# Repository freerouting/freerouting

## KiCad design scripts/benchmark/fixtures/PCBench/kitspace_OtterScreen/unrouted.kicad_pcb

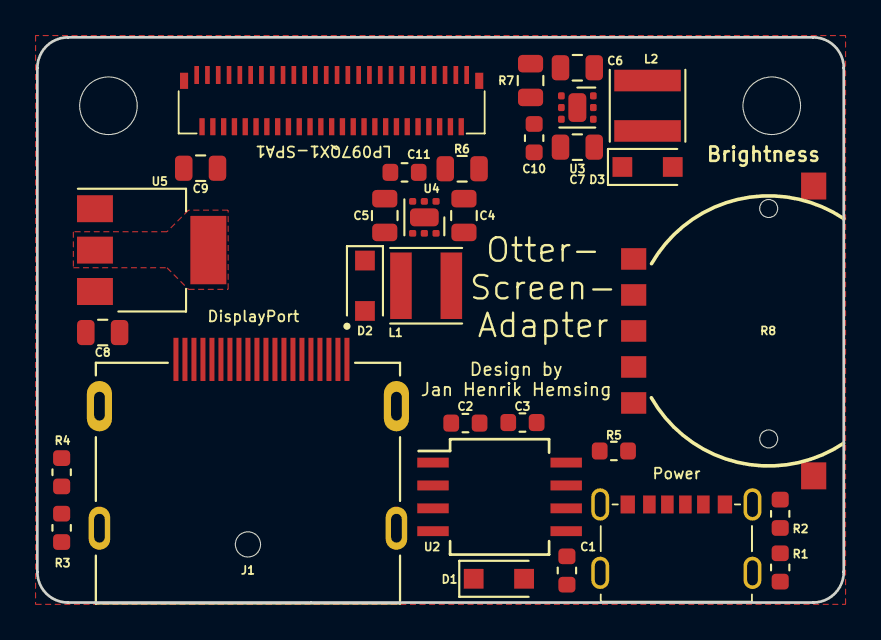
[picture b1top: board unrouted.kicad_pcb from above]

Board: 2 copper layers, 44.8 x 31.4 mm, 33 parts (0 on the bottom side), 31 nets, no tracks yet.

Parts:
C1, C2: 100n; C_0603_1608Metric
C3: 1n; C_0603_1608Metric
C4, C6: 10uF; C_0805_2012Metric
C5, C7, C8, C9: 0.47uF; C_0805_2012Metric
C10, C11: 220nF; C_0603_1608Metric
D1: D; D_SOD-123F
D2, D3: SS34; D_SOD-123F
H1, H2: MountingHole_Pad; MountingHole_3.2mm_M3
J1: 47272-0001; MOLEX_47272-0001
J2: USB-C_Power
L1, L2: 22uH; L_Taiyo-Yuden_MD-4040
R1, R2: 5K1; R_0603_1608Metric
R3, R4: 0; R_0603_1608Metric
R5: 100; R_0603_1608Metric
R6, R7: 0.8; R_0805_2012Metric
R8: RK14J12R0A09
U1: 5022505191
U2: NE555; SO-8_5.3x6.2mm_P1.27mm
U3, U4: TPS61160A; WSON-6-1EP_2x2mm_P0.65mm_EP1x1.6mm
U5: AMS1117-3.3; SOT-223-3_TabPin2

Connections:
+3V3: C9.1, U1.4, U1.5, U1.6, U1.7, U5.2
+5V: C2.1, C4.1, C6.1, C8.1, J2.2, J2.5, L1.1, L2.1, R5.1, U2.4, U2.8, U3.6, U4.6, U5.3
AUX_N: J1.17, U1.10
AUX_P: J1.15, U1.9
GND: C1.2, C2.2, C3.2, C4.2, C5.2, C6.2, C7.2, C8.2, C9.2, C10.2, C11.2, H1.1, H2.1, J1.2, J1.5, J1.8, J1.11, J1.16, J1.19, J1.S1, J1.S2, J1.S3, J1.S4, J2.1, J2.6, J2.7, R1.2, R2.2, R3.2, R4.2, R6.2, R7.2, U1.1, U1.3, U1.8, U1.11, U1.15, U1.19, U1.23, U1.27, U1.28, U1.29, U1.36, U1.43, U1.51, U2.1, U3.3, U3.7, U4.3, U4.7, U5.1
HPD: J1.18, U1.2
L0_N: J1.10, U1.12
L0_P: J1.12, U1.14
L1_N: J1.7, U1.16
L1_P: J1.9, U1.18
L2_N: J1.4, U1.20
L2_P: J1.6, U1.22
L3_N: J1.1, U1.24
L3_P: J1.3, U1.26
LEDA1: C5.1, D2.1, U1.48, U1.49
LEDA2: C7.1, D3.1, U1.45, U1.46
LEDC1: R6.1, U1.37, U1.38, U1.39, U1.40, U1.41, U1.42, U4.1
LEDC2: R7.1, U1.30, U1.31, U1.32, U1.33, U1.34, U1.35, U3.1
unnamed: C1.1, U2.5
unnamed: C3.1, D1.1, R8.1, U2.2, U2.6
unnamed: C10.1, U3.2
unnamed: C11.1, U4.2
unnamed: D1.2, R8.2, U2.7
unnamed: D2.2, L1.2, U4.4
unnamed: D3.2, L2.2, U3.4
unnamed: J1.13, R3.1
unnamed: J1.14, R4.1
unnamed: J2.3, R1.1
unnamed: J2.4, R2.1
unnamed: R5.2, R8.3
PWM: U2.3, U3.5, U4.5

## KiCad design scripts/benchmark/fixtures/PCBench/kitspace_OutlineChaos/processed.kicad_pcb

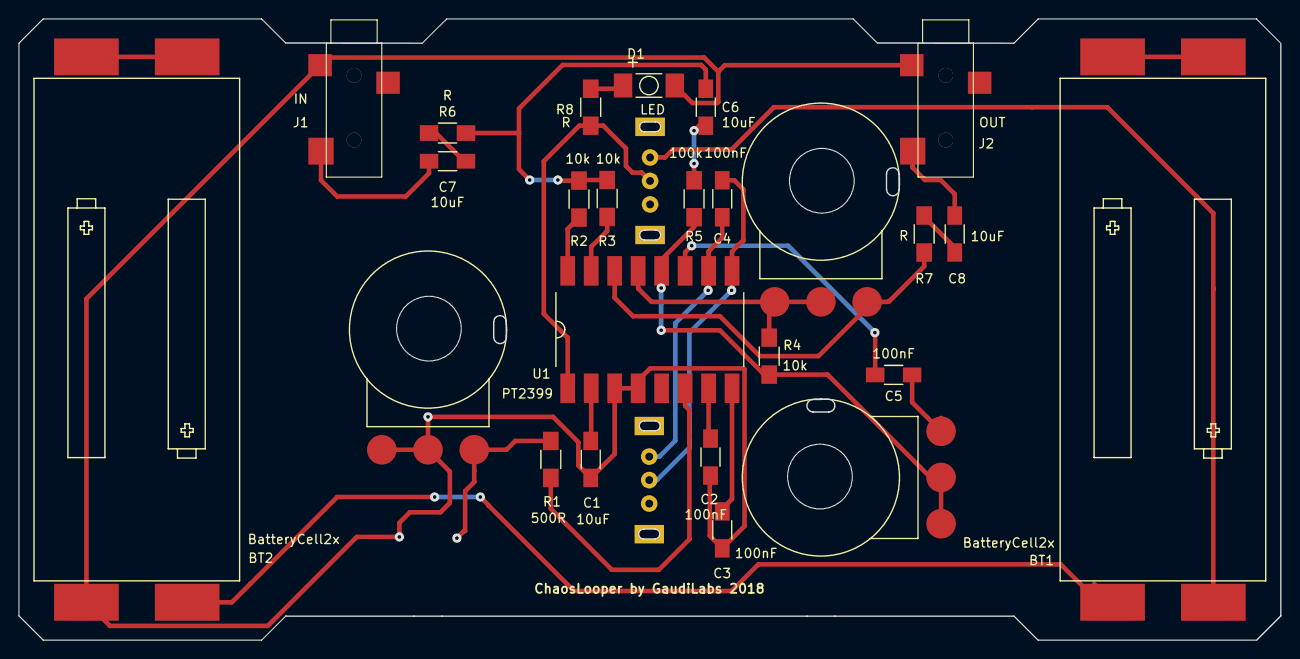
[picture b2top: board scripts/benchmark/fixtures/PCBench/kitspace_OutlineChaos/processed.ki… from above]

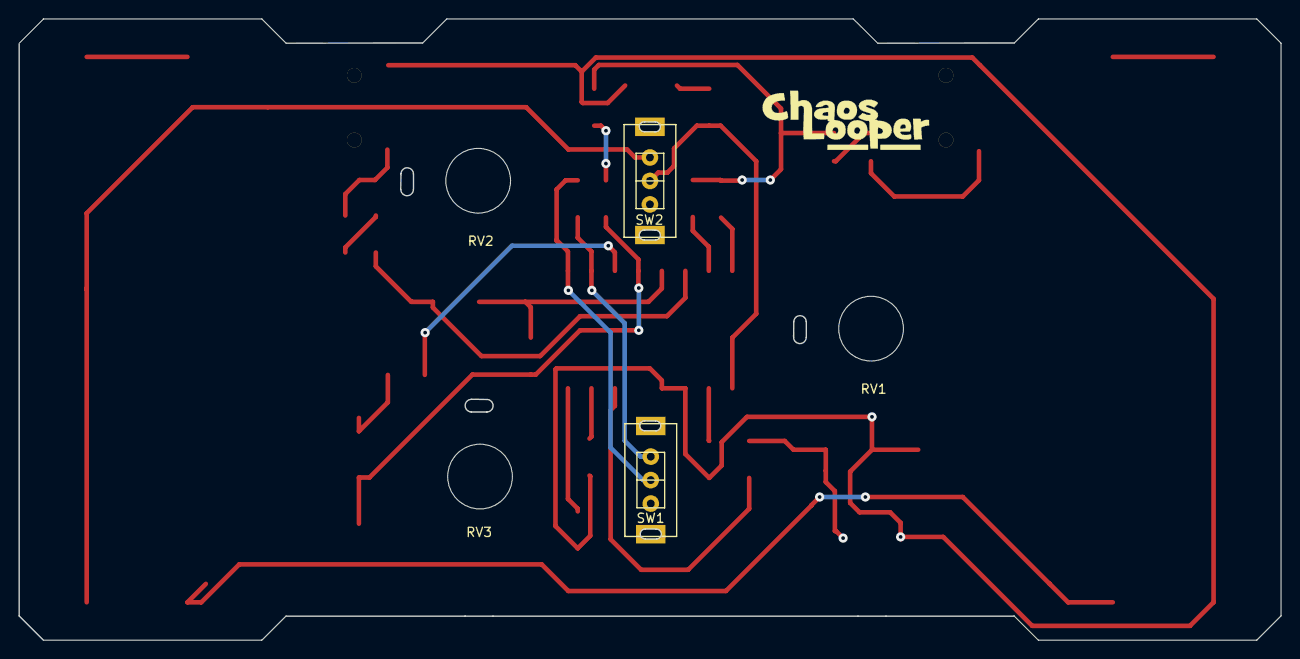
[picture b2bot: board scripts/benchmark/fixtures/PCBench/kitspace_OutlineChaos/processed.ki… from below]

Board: 2 copper layers, 136.5 x 67.2 mm, 27 parts (5 on the bottom side), 27 nets.

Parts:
BT1, BT2: BatteryCell2x; BAT_HOLDER_AAA_DOUBLE
C1, C6, C7, C8: 10uF; C_1206_HandSoldering
C2, C3, C4, C5: 100nF; C_1206_HandSoldering
D1: LED; TOPLED_R
J1: IN; PLUG3_5_SwitchCraft_2B
J2: OUT; PLUG3_5_SwitchCraft_2B
R1: 500R; R_1206_HandSoldering
R2, R3, R4: 10k; R_1206_HandSoldering
R5: 100k; R_1206_HandSoldering
R6, R7, R8: R; R_1206_HandSoldering
RV1: SPEED_POT; POTI_PCB
RV2: VOL_POT; POTI_PCB
RV3: POT; POTI_PCB
SW1, SW2: Switch; SWITCH_SLIDE
U1: PT2399; DIL16_SMD

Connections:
GND: BT2.4, C1.2, C2.1, C3.1, D1.1, J1.1, J2.1, RV1.2, RV1.3, U1.3, U1.4
unnamed: BT1.1, SW2.1
unnamed: BT1.2, BT1.3
unnamed: BT1.4, BT2.1
unnamed: BT2.2, BT2.3
unnamed: C1.1, U1.2
unnamed: C2.2, U1.7
unnamed: C3.2, U1.8
unnamed: C4.1, SW1.2, U1.9
unnamed: C4.2, SW1.1, U1.10
unnamed: C5.1, RV3.1
unnamed: C5.2, U1.11
unnamed: C6.1, R2.1, R3.1, R6.2
unnamed: C6.2, R5.1
unnamed: C7.1, J1.3
unnamed: C7.2, R6.1
unnamed: C8.1, J2.3
unnamed: C8.2, R7.1
unnamed: D1.2, R8.1
unnamed: R1.1, RV1.1
unnamed: R1.2, U1.6
unnamed: R2.2, U1.16
unnamed: R3.2, U1.15
unnamed: R4.1, R5.2, RV3.2, RV3.3, U1.12
unnamed: R4.2, RV2.2, RV2.3, U1.13
unnamed: R7.2, RV2.1, U1.14
VCC: R8.2, SW2.2, U1.1

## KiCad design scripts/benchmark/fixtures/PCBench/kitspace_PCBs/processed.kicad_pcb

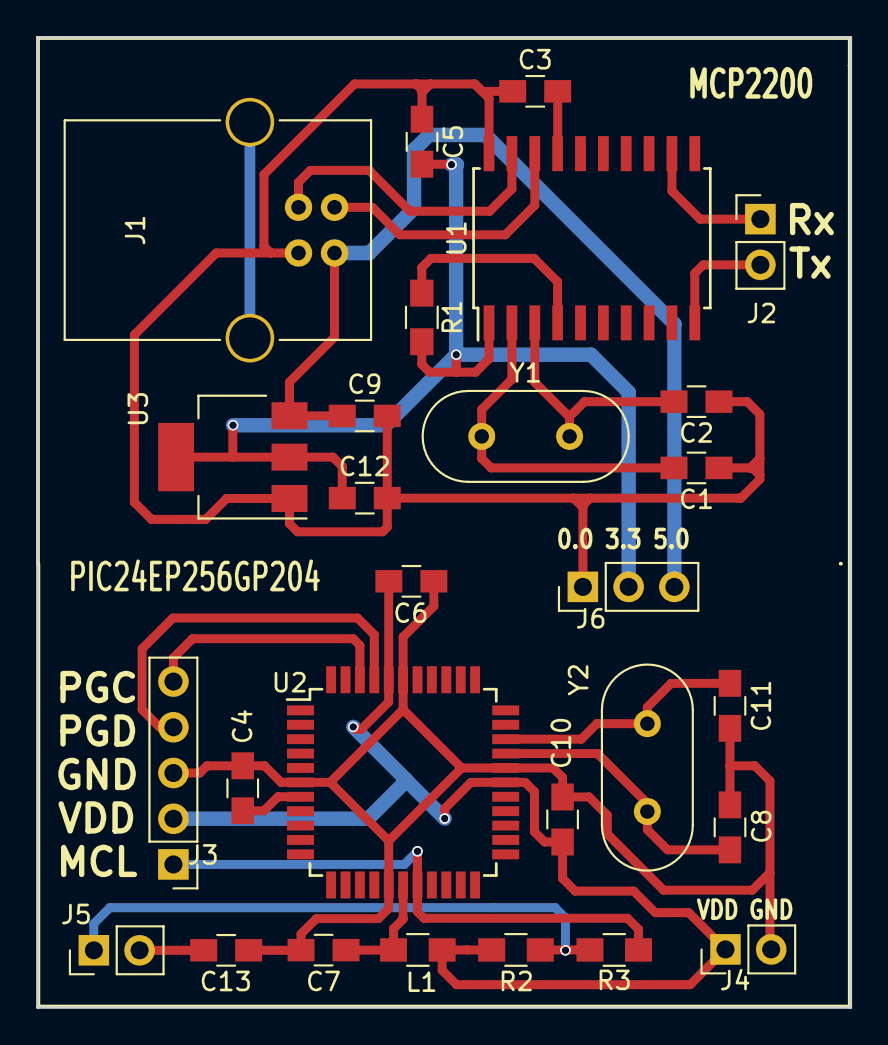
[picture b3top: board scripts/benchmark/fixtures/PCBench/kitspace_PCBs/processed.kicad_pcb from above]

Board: 2 copper layers, 45.2 x 53.9 mm, 28 parts (0 on the bottom side), 22 nets.

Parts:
C1, C2, C8, C11: 15p; C_0805_HandSoldering
C3, C5, C6, C7, C10, C13: 0.1u; C_0805_HandSoldering
C4, C12: 10u; C_0805_HandSoldering
C9: 1u; C_0805_HandSoldering
J1: USB; USB_B
J2: Tx_Rx; Pin_Header_Straight_1x02_Pitch2.54mm
J3: Programmer; Pin_Header_Straight_1x05_Pitch2.54mm
J4: Power; Pin_Header_Straight_1x02_Pitch2.54mm
J5: MCLR_J; Pin_Header_Straight_1x02_Pitch2.54mm
J6: Power; Pin_Header_Straight_1x03_Pitch2.54mm
L1: 10uH; L_0805_HandSoldering
R1: 4.7k; R_0805_HandSoldering
R2: 9k8; R_0805_HandSoldering
R3: 330; R_0805_HandSoldering
U1: MCP2200; SOIC-20W_7.5x12.8mm_Pitch1.27mm
U2: PIC24EP64GP204; TQFP-44_10x10mm_Pitch0.8mm
U3: LM1117-3.3; SOT-223
Y1, Y2: Crystal; Crystal_HC49-4H_Vertical

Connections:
D+: J1.3, U1.19
D-: J1.2, U1.18
GND: C4.2, C6.1, C7.2, C8.2, C10.1, C11.2, C13.2, J3.3, J4.2, U2.6, U2.16, U2.29, U2.39
MCLR: J3.1, R3.1, U2.18
MCL_A: J5.1, R2.1, R3.2
MCL_B: C13.1, J5.2
unnamed: C3.2, U1.17
unnamed: C4.1, U2.7
unnamed: C7.1, L1.1, U2.17
unnamed: R1.1, U1.4
OS1: C1.2, U1.2, Y1.1
OS2: C2.2, U1.3, Y1.2
OSC1: C8.1, U2.30, Y2.1
OSC2: C11.1, U2.31, Y2.2
PGC: J3.5, U2.42
PGD: J3.4, U2.41
Rx: J2.1, U1.12
Tx: J2.2, U1.10
V+: C5.2, C12.1, J6.2, R1.2, U1.1, U3.2, U3.4
V-: C1.1, C2.1, C3.1, C5.1, C9.2, C12.2, J1.4, J6.1, U1.20, U3.1
VBus: C9.1, J1.1, J6.3, U3.3
VDD: C6.2, C10.2, J3.2, J4.1, L1.2, R2.2, U2.28, U2.40

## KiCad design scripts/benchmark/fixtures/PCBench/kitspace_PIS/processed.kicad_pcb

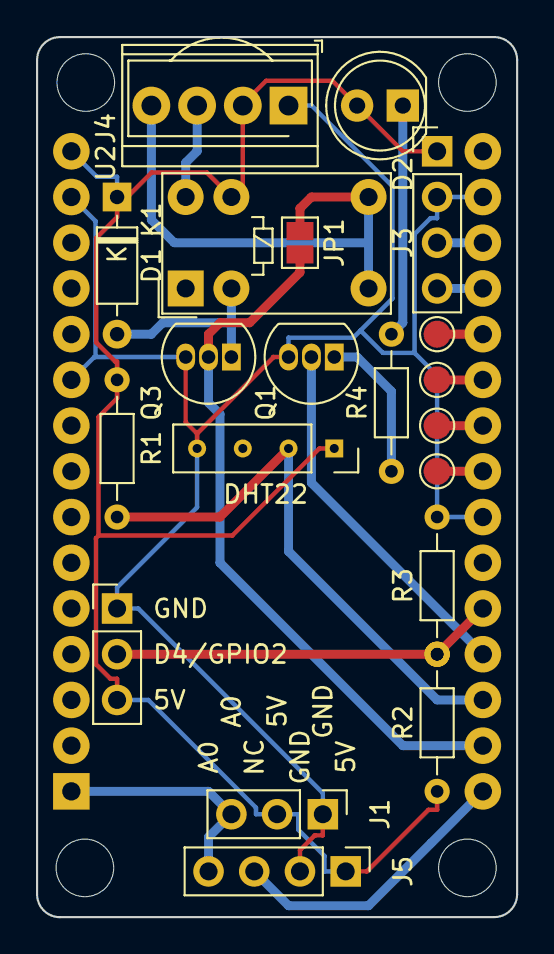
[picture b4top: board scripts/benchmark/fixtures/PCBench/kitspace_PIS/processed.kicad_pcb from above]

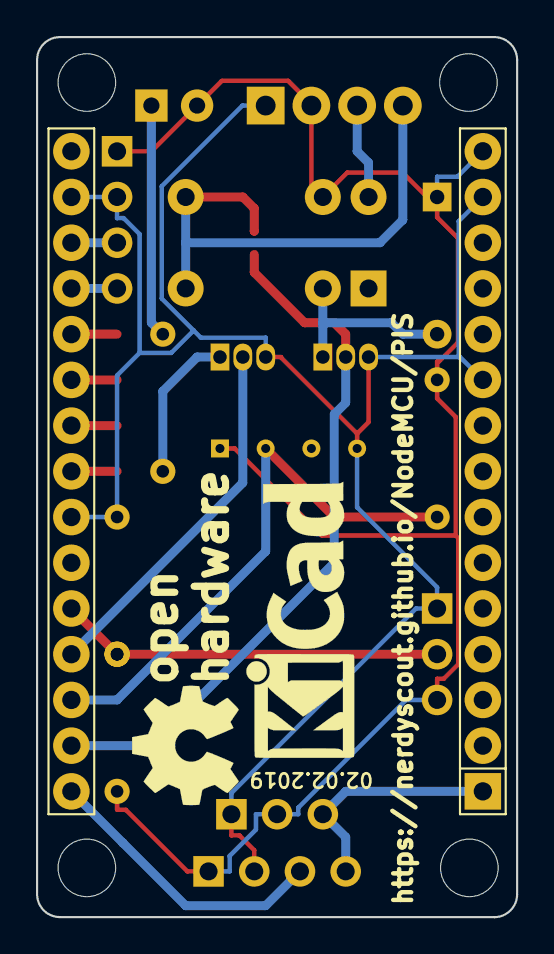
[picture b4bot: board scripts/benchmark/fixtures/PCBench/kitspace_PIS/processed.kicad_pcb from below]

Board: 2 copper layers, 26.7 x 48.9 mm, 24 parts (3 on the bottom side), 19 nets.

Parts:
D1: 1N4148; D_DO-35_SOD27_P7.62mm_Horizontal
D2: LED; LED_D5.0mm
J1: Capacitive Sensor; PinHeader_1x03_P2.54mm_Vertical
J2: Conn_01x03; PinHeader_1x03_P2.54mm_Vertical
J3: Serial; PinHeader_1x04_P2.54mm_Vertical
J4: Screw_Terminal_01x04; TerminalBlock_TE_282834-4_1x04_P2.54mm_Horizontal
J5: Resistive Sensor; PinHeader_1x04_P2.54mm_Vertical
JP1: NO; SolderJumper-2_P1.3mm_Open_Pad1.0x1.5mm
K1: G5V-1; Relay_SPDT_Omron_G5V-1
LOGO1: Logo_Open_Hardware_Small; OSHW-Symbol_6.7x6mm_SilkScreen
LOGO2: Logo_Open_Hardware_Small; KiCad-Logo_6mm_SilkScreen
Q1, Q3: BC547; TO-92_Inline
R1, R2, R3: 10k; R_Axial_DIN0204_L3.6mm_D1.6mm_P7.62mm_Horizontal
R4: 100; R_Axial_DIN0204_L3.6mm_D1.6mm_P7.62mm_Horizontal
TP1: CLK; TestPoint_Pad_D1.5mm
TP2: MISO; TestPoint_Pad_D1.5mm
TP3: MOSI; TestPoint_Pad_D1.5mm
TP4: CS; TestPoint_Pad_D1.5mm
U1: NodeMCU1.0(ESP-12E); NodeMCU_Amica
U2: TSOP17xx; Vishay_CAST-3Pin
U4: DHT11; PinSocket_1x04_P2.54mm_Vertical

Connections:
+5V: D1.1, D2.2, J1.2, J2.3, J3.1, J4.2, J5.1, K1.9, R1.2, R2.2, U1.15, U2.2, U4.1
A0: J1.3, J5.4, U1.1
Contact: J2.2, R2.1, R3.2, U1.26
DHT: R1.1, U1.28, U4.2
Dig: J5.3, U1.30
GND: J1.1, J2.1, J3.2, J4.1, J5.2, Q1.3, Q3.3, R3.1, U1.10, U1.14, U1.17, U1.24, U2.1, U4.4
LED: Q1.2, U1.27
unnamed: D1.2, K1.2, Q3.1
unnamed: D2.1, R4.2
unnamed: J4.3, K1.10
unnamed: J4.4, JP1.2, K1.5, K1.6, U2.3
unnamed: Q1.1, R4.1
unnamed: TP1.1, U1.23
unnamed: TP2.1, U1.22
unnamed: TP3.1, U1.21
unnamed: TP4.1, U1.20
Relay: JP1.1, Q3.2, U1.29
RxD: J3.4, U1.19
TxD: J3.3, U1.18
